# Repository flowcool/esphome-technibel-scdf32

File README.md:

**[🇬🇧 English](#-english)** · **[🇫🇷 Français](#-français)**

---

# ESPHome — Technibel SCDF32C5I IR Climate

> Fully reverse-engineered IR protocol + complete ESPHome / Home Assistant integration.  
> Protocole IR entièrement décodé + intégration ESPHome / Home Assistant complète.

---

## 🇬🇧 English

### What this is

This repository provides everything needed to control a **Technibel SCDF32C5I**
split air conditioner from Home Assistant using an ESP32 as an IR blaster.

The IR protocol was fully reverse-engineered from raw captures — Technibel uses a
**proprietary 48-bit protocol** that is not recognized by IRremoteESP8266. The frame
structure, encoding, and checksum formula are documented in [`docs/protocol.md`](docs/protocol.md).

**What you get:**
- `technibel_ir.h` — C++ IR frame builder (48-bit, checksum included)
- `ir-technibel-clim.yaml` — ESPHome transmitter config exposing a `send_command` service
- `ir-clim-sniffer.yaml` — ESPHome receiver config for capturing raw IR frames (debug use)
- `climate-technibel-ha.yaml` — Home Assistant MQTT climate entity (full package)

### Hardware (BOM)

See [`docs/bom.md`](docs/bom.md) for the full bill of materials.

| Component | Reference | Notes |
|---|---|---|
| MCU | ESP32 DevKit 30-pin | Any ESP32 board works |
| IR emitter | Diymore PCB0100 (2-channel) | Transistor + resistors built-in |
| IR receiver | KY-022 / VS1838B 38kHz | Sniffer phase only, not needed in final build |
| Capacitor | 100µF 16V electrolytic | Power filtering near TX module |

### Wiring

See [`docs/wiring.md`](docs/wiring.md) for the full ASCII diagram.

```
ESP32 GPIO4  ──► Diymore PCB0100 IN1   (IR transmitter)
ESP32 GPIO23 ◄── KY-022 OUT            (IR receiver — sniffer only)
```

### Installation

1. Copy `esphome/libraries/technibel_ir.h` to your ESPHome `config/libraries/` directory.
2. Flash `esphome/ir-technibel-clim.yaml` to your ESP32.
3. Add your `wifi_ssid`, `wifi_password`, and `ota_password` to your `secrets.yaml`.
4. In Home Assistant, add `homeassistant/climate-technibel-ha.yaml` to your packages directory.
5. Restart Home Assistant. The `climate.clim_sejour` entity will appear.

> **Note:** Adjust `sensor.thermometre_espace_de_vie_temperature` in `climate-technibel-ha.yaml`
> to match your own ambient temperature sensor entity ID.

### Usage in Home Assistant

Once installed, `climate.clim_sejour` supports:

| Feature | Values |
|---|---|
| HVAC modes | `off`, `cool`, `dry`, `fan_only`, `auto` |
| Fan modes | `auto`, `1`, `2`, `3`, `4`, `5`, `6` |
| Temperature range | 16°C – 30°C (1°C step) |
| Current temperature | From your HA temperature sensor |

Every state change (mode, temperature, fan speed) automatically sends the full IR
command to the AC via the ESP32.

### Protocol regression check

Run the dependency-free protocol verifier after changing captures, documentation,
or frame-generation code. It does not compile ESPHome or contact live devices:

```bash
python3 tests/verify_protocol.py
```

### Protocol overview

The Technibel SCDF32C5I uses a proprietary 48-bit IR protocol at 38kHz.
Frame: `B0 B1 B2 B3 B4 B5` (6 bytes). Checksum includes ambient temperature.

→ Full details in [`docs/protocol.md`](docs/protocol.md)

---

## 🇫🇷 Français

### Description

Ce dépôt contient tout le nécessaire pour piloter un climatiseur **Technibel SCDF32C5I**
depuis Home Assistant via un ESP32 émetteur IR.

Le protocole IR a été entièrement décodé par reverse engineering — Technibel utilise un
**protocole propriétaire 48 bits** non reconnu par IRremoteESP8266. C'est probablement
la première documentation publique de ce protocole.

**Contenu :**
- `technibel_ir.h` — constructeur de trames IR en C++ (48 bits, checksum inclus)
- `ir-technibel-clim.yaml` — config ESPHome émetteur, expose un service `send_command`
- `ir-clim-sniffer.yaml` — config ESPHome récepteur pour capture de trames brutes (debug)
- `climate-technibel-ha.yaml` — entité climate MQTT pour Home Assistant (package complet)

### Matériel (BOM)

Voir [`docs/bom.md`](docs/bom.md) pour la liste complète.

| Composant | Référence | Notes |
|---|---|---|
| MCU | ESP32 DevKit 30 broches | N'importe quel ESP32 fonctionne |
| Émetteur IR | Diymore PCB0100 (2 canaux) | Transistor + résistances intégrés |
| Récepteur IR | KY-022 / VS1838B 38kHz | Phase sniffer uniquement, inutile en prod |
| Condensateur | 100µF 16V électrolytique | Filtrage alim près du module TX |

### Câblage

Voir [`docs/wiring.md`](docs/wiring.md) pour le schéma ASCII complet.

```
ESP32 GPIO4  ──► Diymore PCB0100 IN1   (émetteur IR)
ESP32 GPIO23 ◄── KY-022 OUT            (récepteur IR — sniffer uniquement)
```

### Installation

1. Copier `esphome/libraries/technibel_ir.h` dans le dossier `config/libraries/` de votre ESPHome.
2. Flasher `esphome/ir-technibel-clim.yaml` sur votre ESP32.
3. Ajouter vos `wifi_ssid`, `wifi_password` et `ota_password` dans `secrets.yaml`.
4. Dans Home Assistant, ajouter `homeassistant/climate-technibel-ha.yaml` dans votre dossier `packages/`.
5. Redémarrer Home Assistant. L'entité `climate.clim_sejour` apparaît.

> **Note :** Remplacer `sensor.thermometre_espace_de_vie_temperature` dans `climate-technibel-ha.yaml`
> par l'entity_id de votre propre capteur de température ambiante.

### Utilisation dans Home Assistant

L'entité `climate.clim_sejour` une fois installée supporte :

| Fonction | Valeurs |
|---|---|
| Modes HVAC | `off`, `cool`, `dry`, `fan_only`, `auto` |
| Vitesses ventilateur | `auto`, `1`, `2`, `3`, `4`, `5`, `6` |
| Plage température | 16°C – 30°C (pas 1°C) |
| Température courante | Depuis votre capteur HA |

### Vérification de non-régression du protocole

Après toute modification des captures, de la documentation ou du générateur de
trames, lancer le vérificateur sans dépendance. Il ne compile pas ESPHome et ne
contacte aucun appareil :

```bash
python3 tests/verify_protocol.py
```

### Aperçu du protocole

Le Technibel SCDF32C5I utilise un protocole IR propriétaire 48 bits à 38kHz.
Trame : `B0 B1 B2 B3 B4 B5` (6 octets). Le checksum intègre la température ambiante.

→ Documentation complète dans [`docs/protocol.md`](docs/protocol.md)

---

## Protocol summary / Résumé protocole

| Byte | Value | Description |
|---|---|---|
| B0 | `0xD0` | Device address (fixed / fixe) |
| B1 | ambient+mode | High nibble = ambient temperature, low nibble: COOL=`0xC`, DRY=`0xA`, FAN=`0x9`, AUTO=`0xD` |
| B2 | temp+fan | hi nibble = temp encoded, lo nibble = fan speed |
| B3 | `0x18`/`0x08` | Power ON / OFF |
| B4 | `0x03` | Fixed / Fixe |
| B5 | checksum | Includes ambient temperature / Intègre T° ambiante |

→ [`docs/protocol.md`](docs/protocol.md) for full encoding tables and checksum formula.

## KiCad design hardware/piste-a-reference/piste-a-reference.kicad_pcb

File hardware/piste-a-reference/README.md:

# Piste A reference perfboard

This directory is the construction authority for the fresh Phase 10 reference
board. The previous hand-drawn/SVG layout is obsolete and must not be used.

## Orientation and coordinates

- Board: isolated-pad FR4 perfboard, 30 × 70 mm, 10 columns × 24 rows.
- Component-side coordinates: columns `A`–`J` left to right, rows `1`–`24`
  top to bottom.
- The XIAO USB-C connector faces row 1.
- The solder-side PDF is already mirrored to match the board as held with the
  solder side facing the operator. Do not mirror it again.

## XIAO ESP32-C3 pin mapping

The schematic and PCB both represent the complete 2×7 XIAO socket:

| Left row, top to bottom | Function | Right row, top to bottom | Function |
|---:|---|---:|---|
| 1 | D0 | 8 | 5V / VBUS |
| 2 | D1 / GPIO3 | 9 | GND |
| 3 | D2 | 10 | 3V3 |
| 4 | D3 | 14 | D10 |
| 5 | D4 | 13 | D9 |
| 6 | D5 | 12 | D8 |
| 7 | D6 | 11 | D7 |

Only pins 2, 8, 9, and 10 are electrically used by this board. All other XIAO
pins remain available and unconnected.

## Mandatory polarity and pinout

- `Q1` is the Mouser onsemi `BC33740BU`. With the flat face toward the observer
  and leads down: pin 1 = Collector, pin 2 = Base, pin 3 = Emitter (`C-B-E`).
- `D1` must be a fresh Mouser Vishay `TSAL6400`: pin 2/anode/long lead at `F23`;
  pin 1/cathode/short lead/flat side at `G23`.
- `C3`: positive pin 1 at `J19`; negative pin 2/stripe at `I19`.
- `C2` and `C3` are directly across 5V and GND, before `R3`.

## Construction hold point

Before soldering, review these native and textual artifacts together:

1. `piste-a-reference.kicad_sch`
2. `piste-a-reference.kicad_pcb`
3. `wiring-table.md`

The current partially assembled board remains untouched as rollback/evidence.
Construction uses a new perfboard and fresh driver components.

## Verification

Install KiCad 9+ and run:

```bash
./verify-design.sh
```

The gate passes only when ERC reports zero errors/warnings and DRC reports zero
violations, zero unconnected pads, and zero schematic-parity problems.

The generator additionally requires `kicad-sch-api==0.5.6`:

```bash
python3 -m venv /tmp/piste-a-kicad-venv
/tmp/piste-a-kicad-venv/bin/pip install -r requirements.txt
/tmp/piste-a-kicad-venv/bin/python generate_design.py
```

Regeneration is deterministic for component placement, net assignments, and
wire coordinates. KiCad-generated UUIDs in the schematic may differ after a
full regeneration.

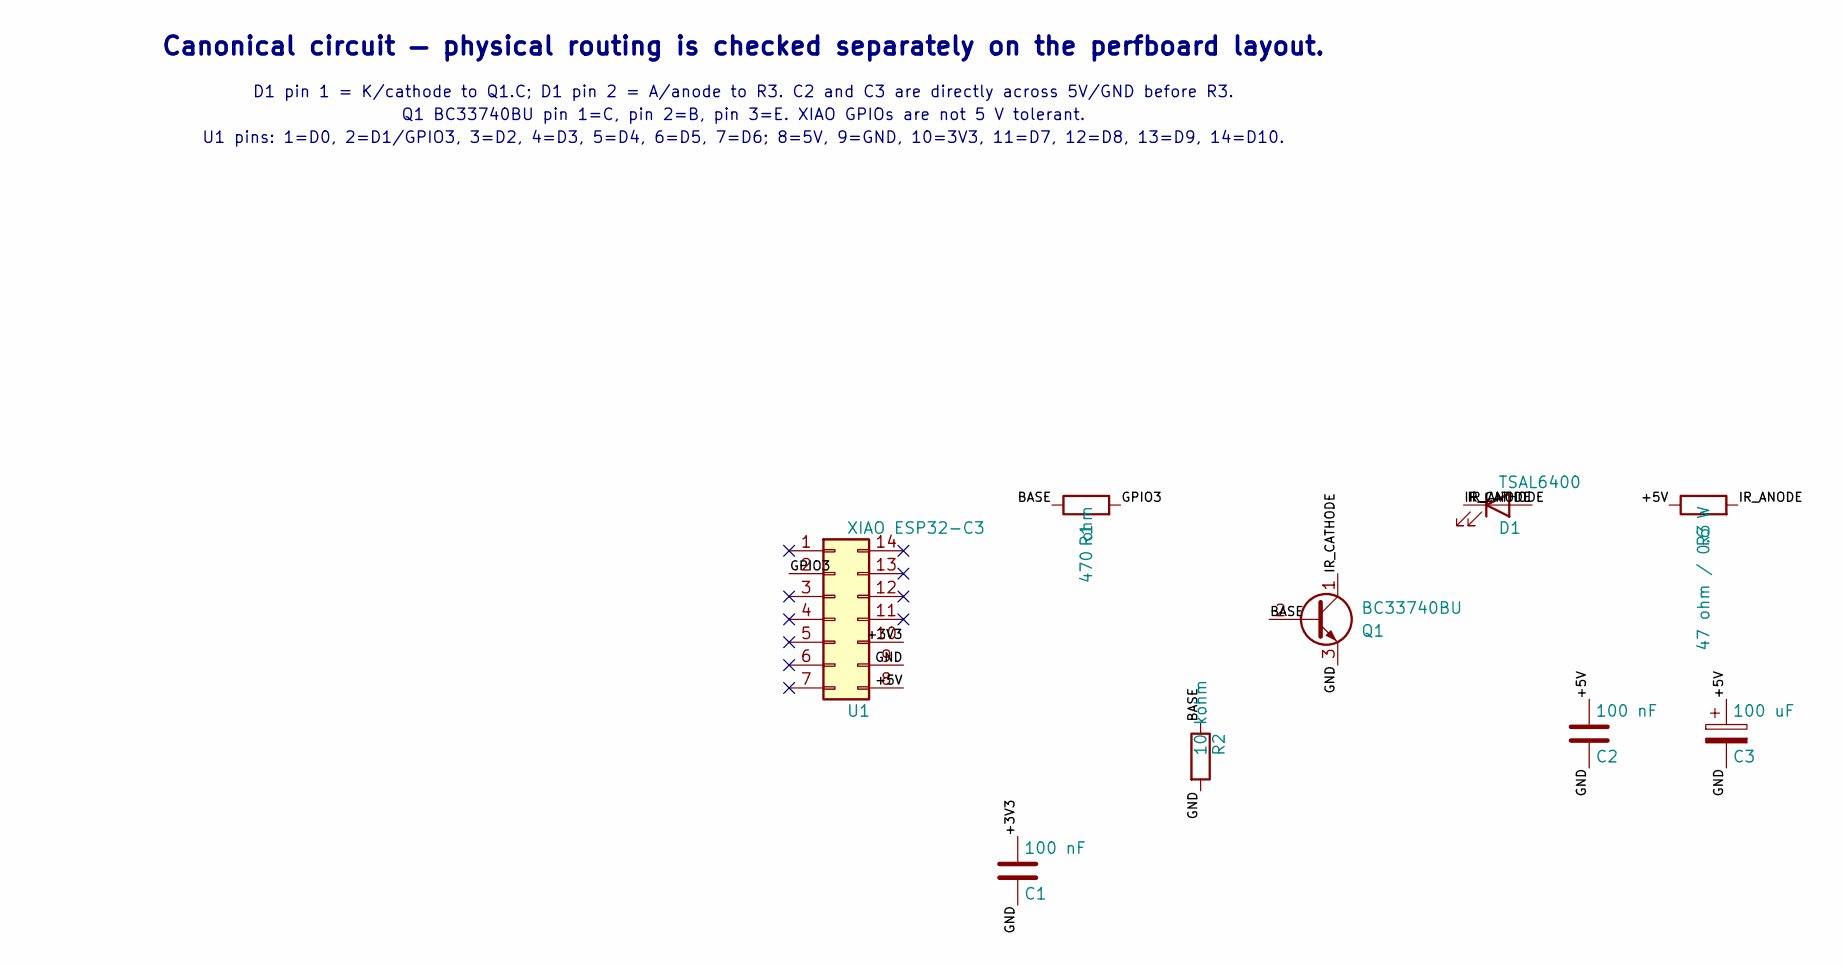
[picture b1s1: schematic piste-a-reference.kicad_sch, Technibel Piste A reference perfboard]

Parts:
C1, C2: 100 nF
C3: 100 uF
D1: TSAL6400
Q1: BC33740BU
R1: 470 ohm
R2: 10 kohm
R3: 47 ohm / 0.6 W
U1: XIAO ESP32-C3

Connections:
+3V3: C1.1, U1.10
+5V: C2.1, C3.1, R3.1, U1.8
BASE: Q1.2 (B), R1.1, R2.1
GND: C1.2, C2.2, C3.2, Q1.3 (E), R2.2, U1.9
GPIO3: R1.2, U1.2
IR_ANODE: D1.2 (A), R3.2
IR_CATHODE: D1.1 (K), Q1.1 (C)

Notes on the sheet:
Canonical circuit — physical routing is checked separately on the perfboard layout.
D1 pin 1 = K/cathode to Q1.C; D1 pin 2 = A/anode to R3. C2 and C3 are directly across 5V/GND before R3.
Q1 BC33740BU pin 1=C, pin 2=B, pin 3=E. XIAO GPIOs are not 5 V tolerant.
U1 pins: 1=D0, 2=D1/GPIO3, 3=D2, 4=D3, 5=D4, 6=D5, 7=D6; 8=5V, 9=GND, 10=3V3, 11=D7, 12=D8, 13=D9, 14=D10.

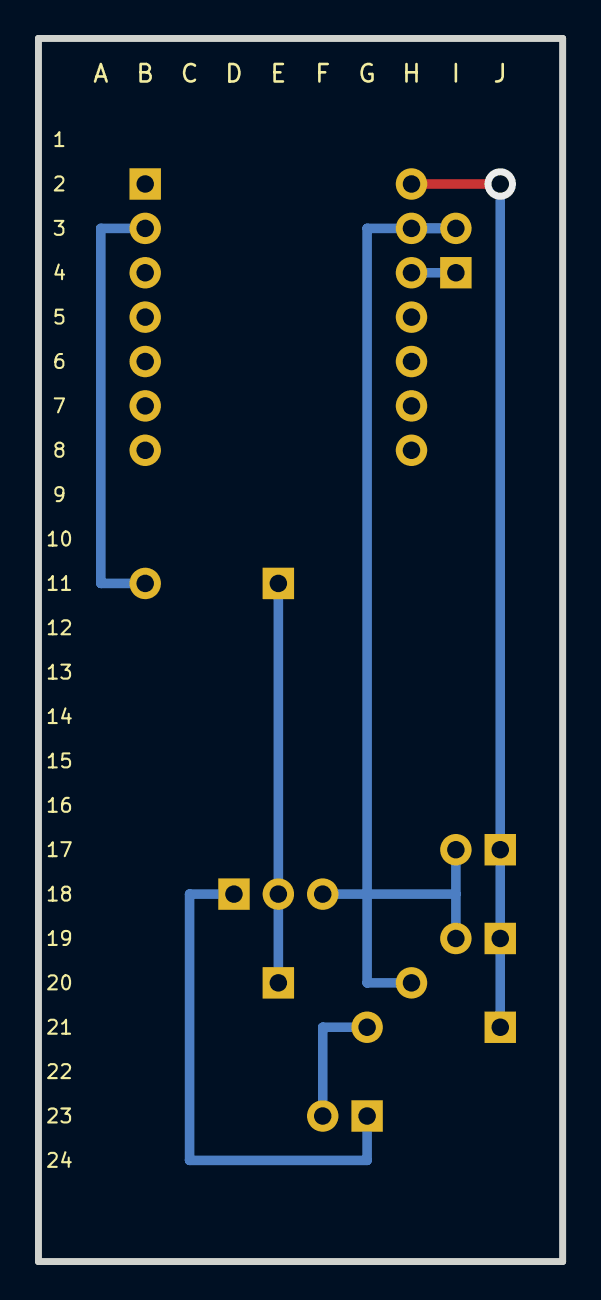
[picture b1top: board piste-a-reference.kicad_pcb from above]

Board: 2 copper layers, 30.0 x 70.0 mm, 9 parts (0 on the bottom side), 7 nets.

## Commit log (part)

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2026-05-28 Initial commit: repo structure, LICENSE, README skeleton
2026-05-28 Add ESPHome and Home Assistant source files
    - esphome/libraries/technibel_ir.h: C++ IR frame builder (48-bit protocol)
    - esphome/ir-technibel-clim.yaml: IR transmitter ESPHome config
    - esphome/ir-clim-sniffer.yaml: IR receiver config for protocol capture
    - homeassistant/climate-technibel-ha.yaml: MQTT climate package for HA
2026-05-28 Add docs/protocol.md: full bilingual IR protocol documentation
    Complete reverse-engineered protocol spec: frame structure, mode/temperature/
    fan encoding, checksum formula (includes ambient temp), OFF frame, timing.
2026-05-28 Add docs/bom.md and docs/wiring.md: bilingual hardware and wiring guide
2026-05-28 Add README_FR.md: French-only full documentation

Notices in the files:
README.md:
License: MIT
